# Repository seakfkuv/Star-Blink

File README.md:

# Star-Blink
Star shaped print with 30 RGB-LEDs

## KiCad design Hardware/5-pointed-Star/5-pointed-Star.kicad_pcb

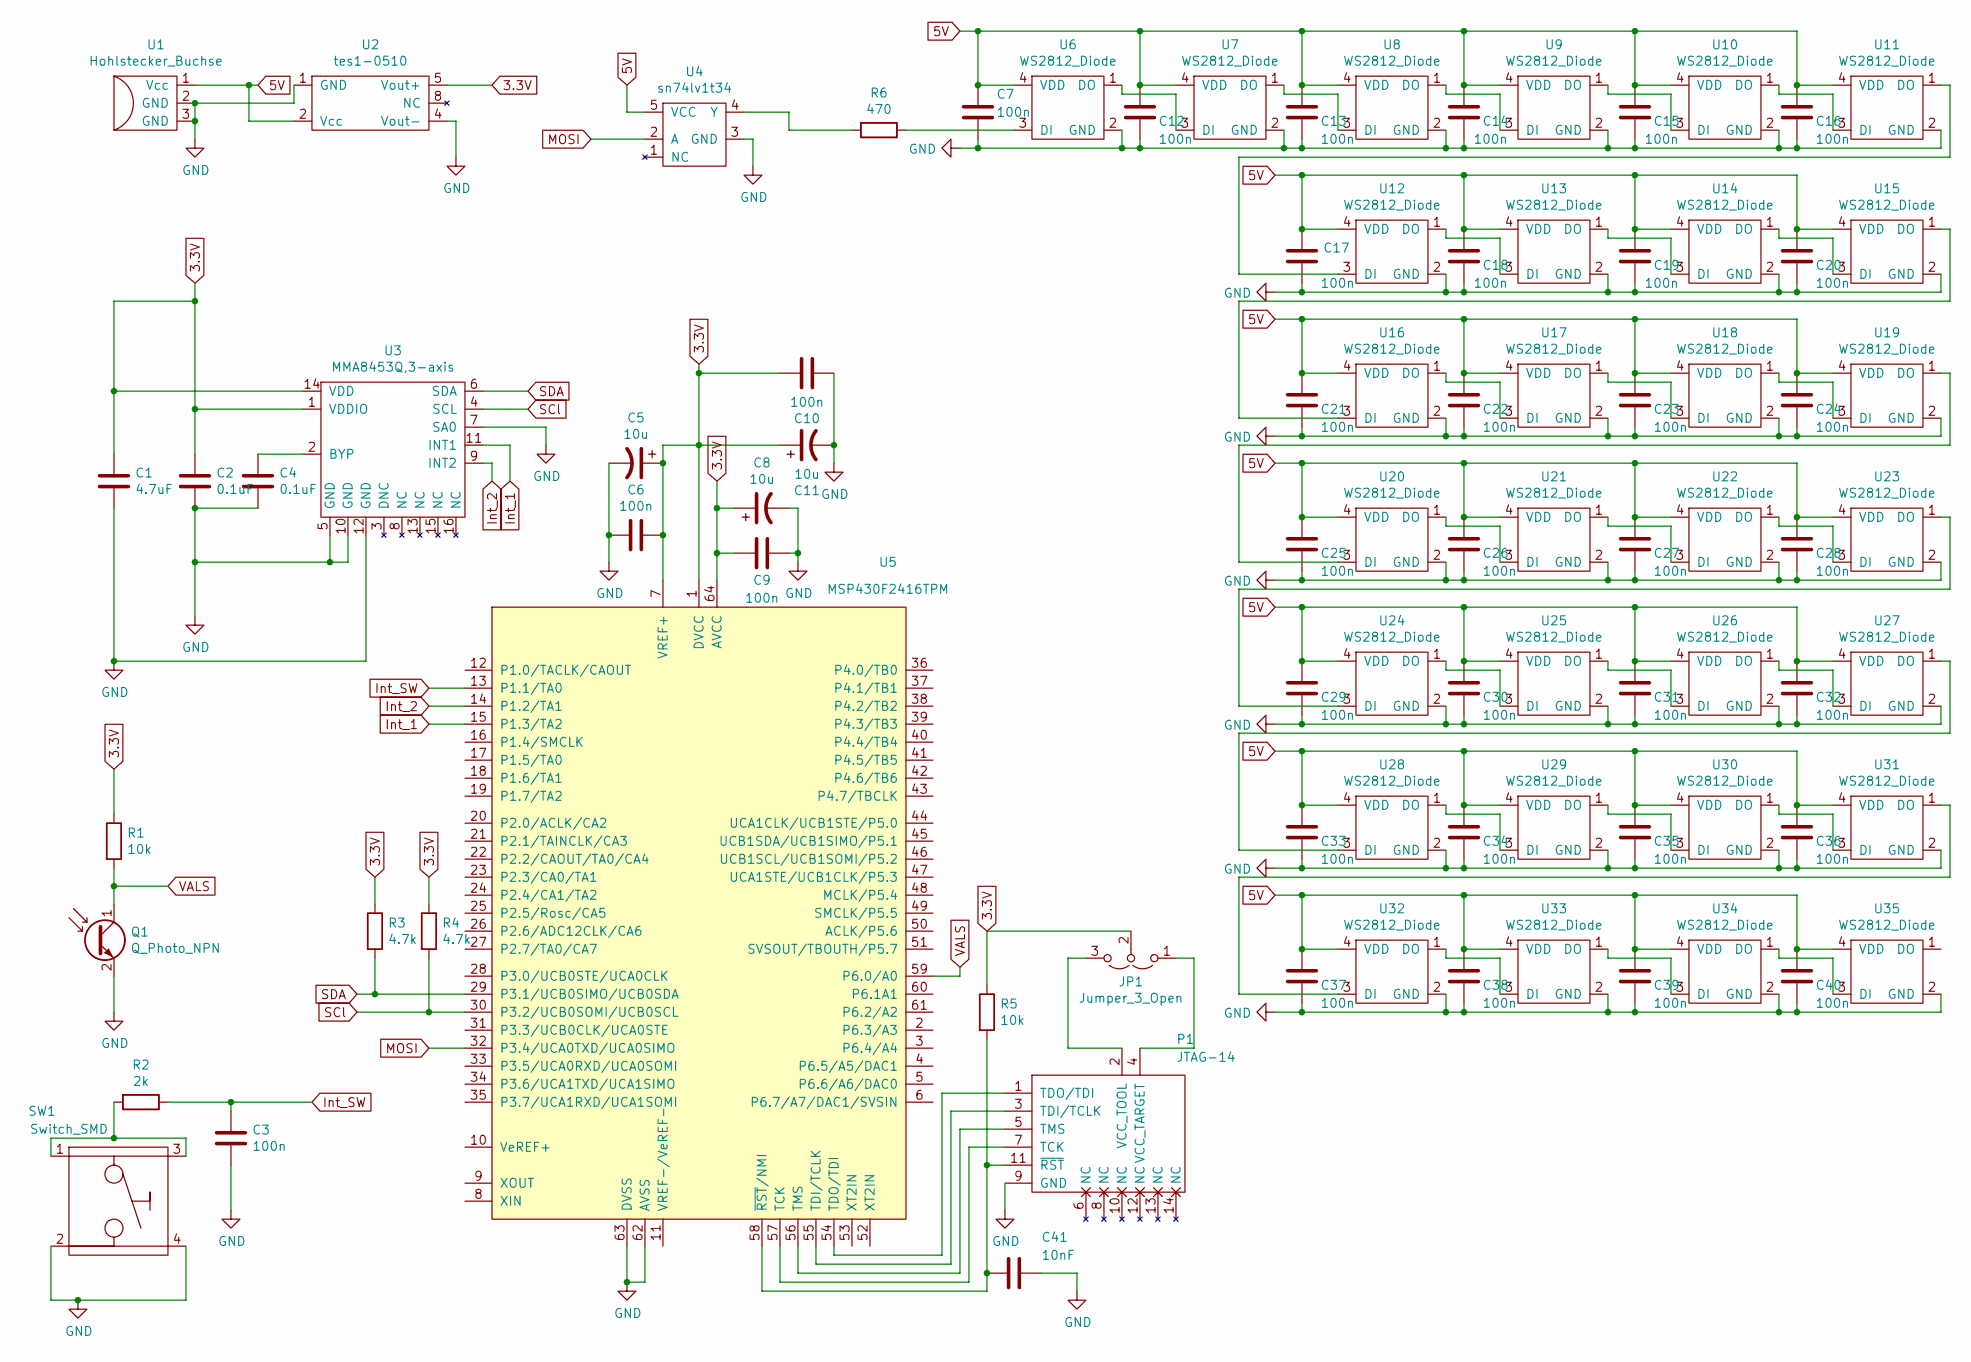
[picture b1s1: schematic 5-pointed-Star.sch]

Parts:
C1: 4.7uF; C_0603_1608Metric
C2, C4: 0.1uF; C_0603_1608Metric
C3, C6, C7, C9, C10, C12, C13, C14, C15, C16, C17, C18, C19, C20, C21, C22, C23, C24, C25, C26, C27, C28, C29, C30, C31, C32, C33, C34, C35, C36, C37, C38, C39, C40: 100n; C_0603_1608Metric
C5, C8, C11: 10u; 865090368008
C41: 10nF; C_0603_1608Metric
JP1: Jumper_3_Open; Jumper_2.54
P1: JTAG-14; JTAG_14
Q1: Q_Photo_NPN; D_0805_2012Metric
R1: 10k; R_0603_1608Metric
R2: 2k; R_0603_1608Metric
R3, R4: 4.7k; R_0603_1608Metric
R5: 10k; R_0603_1608Metric_Pad1.05x0.95mm_HandSolder
R6: 470; R_0603_1608Metric
SW1: Switch_SMD
U1: Hohlstecker_Buchse
U2: tes1-0510
U3: MMA8453Q,3-axis; MMA8453Q
U4: sn74lv1t34; SC70-5
U5: MSP430F2416TPM
U6, U7, U8, U9, U10, U11, U12, U13, U14, U15, U16, U17, U18, U19, U20, U21, U22, U23, U24, U25, U26, U27, U28, U29, U30, U31, U32, U33, U34, U35: WS2812_Diode; WS2812-2020

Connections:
3.3V: C1.1, C2.1, C5.1, C6.1, C8.1, C9.2, C10.1, C11.1, JP1.2 (C), R1.1, R3.1, R4.1, R5.1, U2.5 (Vout+), U3.1 (VDDIO), U3.14 (VDD), U5.1 (DVCC), U5.7 (VREF+), U5.64 (AVCC)
5V: C7.1, C12.1, C13.1, C14.1, C15.1, C16.1, C17.1, C18.1, C19.1, C20.1, C21.1, C22.1, C23.1, C24.1, C25.1, C26.1, C27.1, C28.1, C29.1, C30.1, C31.1, C32.1, C33.1, C34.1, C35.1, C36.1, C37.1, C38.1, C39.1, C40.1, U1.1 (Vcc), U2.2 (Vcc), U4.5 (VCC), U6.4 (VDD), U7.4 (VDD), U8.4 (VDD), U9.4 (VDD), U10.4 (VDD), U11.4 (VDD), U12.4 (VDD), U13.4 (VDD), U14.4 (VDD), U15.4 (VDD), U16.4 (VDD), U17.4 (VDD), U18.4 (VDD), U19.4 (VDD), U20.4 (VDD), U21.4 (VDD), U22.4 (VDD), U23.4 (VDD), U24.4 (VDD), U25.4 (VDD), U26.4 (VDD), U27.4 (VDD), U28.4 (VDD), U29.4 (VDD), U30.4 (VDD), U31.4 (VDD), U32.4 (VDD), U33.4 (VDD), U34.4 (VDD), U35.4 (VDD)
GND: C1.2, C2.2, C3.2, C4.2, C5.2, C6.2, C7.2, C8.2, C9.1, C10.2, C11.2, C12.2, C13.2, C14.2, C15.2, C16.2, C17.2, C18.2, C19.2, C20.2, C21.2, C22.2, C23.2, C24.2, C25.2, C26.2, C27.2, C28.2, C29.2, C30.2, C31.2, C32.2, C33.2, C34.2, C35.2, C36.2, C37.2, C38.2, C39.2, C40.2, C41.1, P1.9 (GND), Q1.2 (E), SW1.2, SW1.4, U1.2 (GND), U1.3 (GND), U2.1 (GND), U2.4 (Vout-), U3.5 (GND), U3.7 (SA0), U3.10 (GND), U3.12 (GND), U4.3 (GND), U5.62 (AVSS), U5.63 (DVSS), U6.2 (GND), U7.2 (GND), U8.2 (GND), U9.2 (GND), U10.2 (GND), U11.2 (GND), U12.2 (GND), U13.2 (GND), U14.2 (GND), U15.2 (GND), U16.2 (GND), U17.2 (GND), U18.2 (GND), U19.2 (GND), U20.2 (GND), U21.2 (GND), U22.2 (GND), U23.2 (GND), U24.2 (GND), U25.2 (GND), U26.2 (GND), U27.2 (GND), U28.2 (GND), U29.2 (GND), U30.2 (GND), U31.2 (GND), U32.2 (GND), U33.2 (GND), U34.2 (GND), U35.2 (GND)
Int_1: U3.11 (INT1), U5.15 (P1.3/TA2)
Int_2: U3.9 (INT2), U5.14 (P1.2/TA1)
Int_SW: C3.1, R2.1, U5.13 (P1.1/TA0)
MOSI: U4.2 (A), U5.32 (P3.4/UCA0TXD/UCA0SIMO)
unnamed: C4.1, U3.2 (BYP)
unnamed: C41.2, P1.11 (~RST), R5.2, U5.58 (~RST~/NMI)
unnamed: JP1.1 (A), P1.4 (VCC_TARGET)
unnamed: JP1.3 (B), P1.2 (VCC_TOOL)
unnamed: P1.1 (TDO/TDI), U5.54 (TDO/TDI)
unnamed: P1.3 (TDI/TCLK), U5.55 (TDI/TCLK)
unnamed: P1.5 (TMS), U5.56 (TMS)
unnamed: P1.7 (TCK), U5.57 (TCK)
unnamed: R2.2, SW1.1, SW1.3
unnamed: R6.1, U6.3 (DI)
unnamed: R6.2, U4.4 (Y)
unnamed: U6.1 (DO), U7.3 (DI)
unnamed: U7.1 (DO), U8.3 (DI)
unnamed: U8.1 (DO), U9.3 (DI)
unnamed: U10.1 (DO), U11.3 (DI)
unnamed: U9.1 (DO), U10.3 (DI)
unnamed: U11.1 (DO), U12.3 (DI)
unnamed: U12.1 (DO), U13.3 (DI)
unnamed: U13.1 (DO), U14.3 (DI)
unnamed: U14.1 (DO), U15.3 (DI)
unnamed: U15.1 (DO), U16.3 (DI)
unnamed: U16.1 (DO), U17.3 (DI)
unnamed: U17.1 (DO), U18.3 (DI)
unnamed: U18.1 (DO), U19.3 (DI)
unnamed: U19.1 (DO), U20.3 (DI)
unnamed: U20.1 (DO), U21.3 (DI)
unnamed: U21.1 (DO), U22.3 (DI)
unnamed: U22.1 (DO), U23.3 (DI)
unnamed: U23.1 (DO), U24.3 (DI)
unnamed: U24.1 (DO), U25.3 (DI)
unnamed: U25.1 (DO), U26.3 (DI)
unnamed: U26.1 (DO), U27.3 (DI)
unnamed: U27.1 (DO), U28.3 (DI)
unnamed: U28.1 (DO), U29.3 (DI)
unnamed: U29.1 (DO), U30.3 (DI)
unnamed: U30.1 (DO), U31.3 (DI)
unnamed: U31.1 (DO), U32.3 (DI)
unnamed: U32.1 (DO), U33.3 (DI)
unnamed: U33.1 (DO), U34.3 (DI)
unnamed: U34.1 (DO), U35.3 (DI)
SCl: R4.2, U3.4 (SCL), U5.30 (P3.2/UCB0SOMI/UCB0SCL)
SDA: R3.2, U3.6 (SDA), U5.29 (P3.1/UCB0SIMO/UCB0SDA)
VALS: Q1.1 (C), R1.2, U5.59 (P6.0/A0)

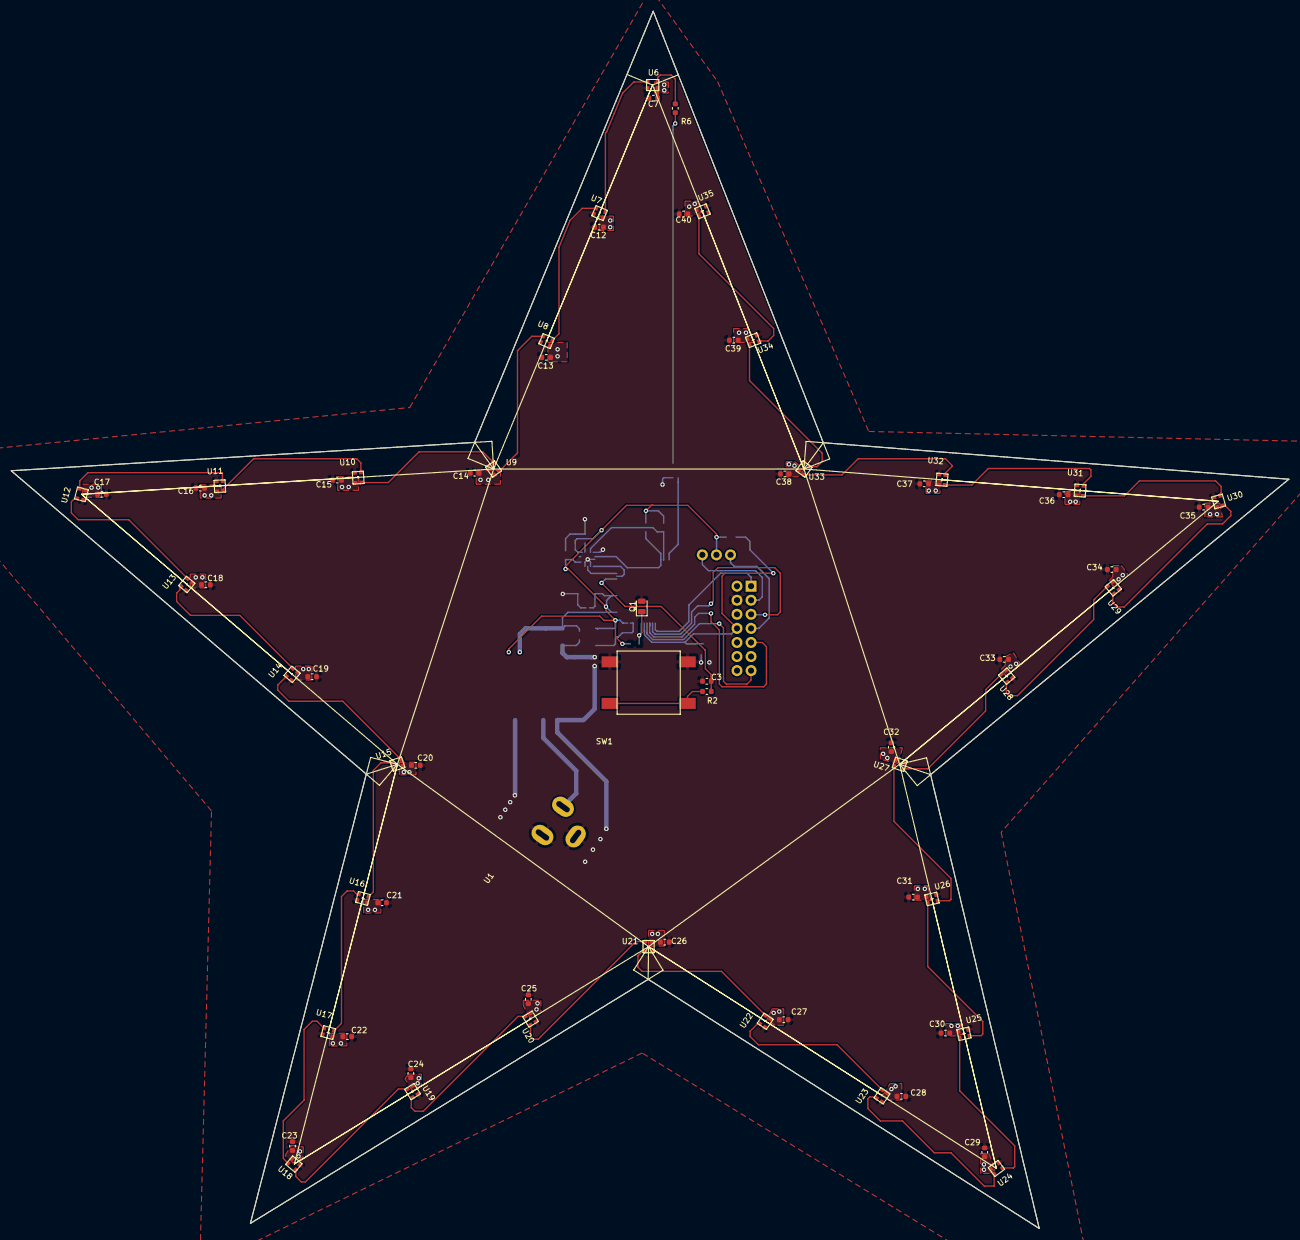
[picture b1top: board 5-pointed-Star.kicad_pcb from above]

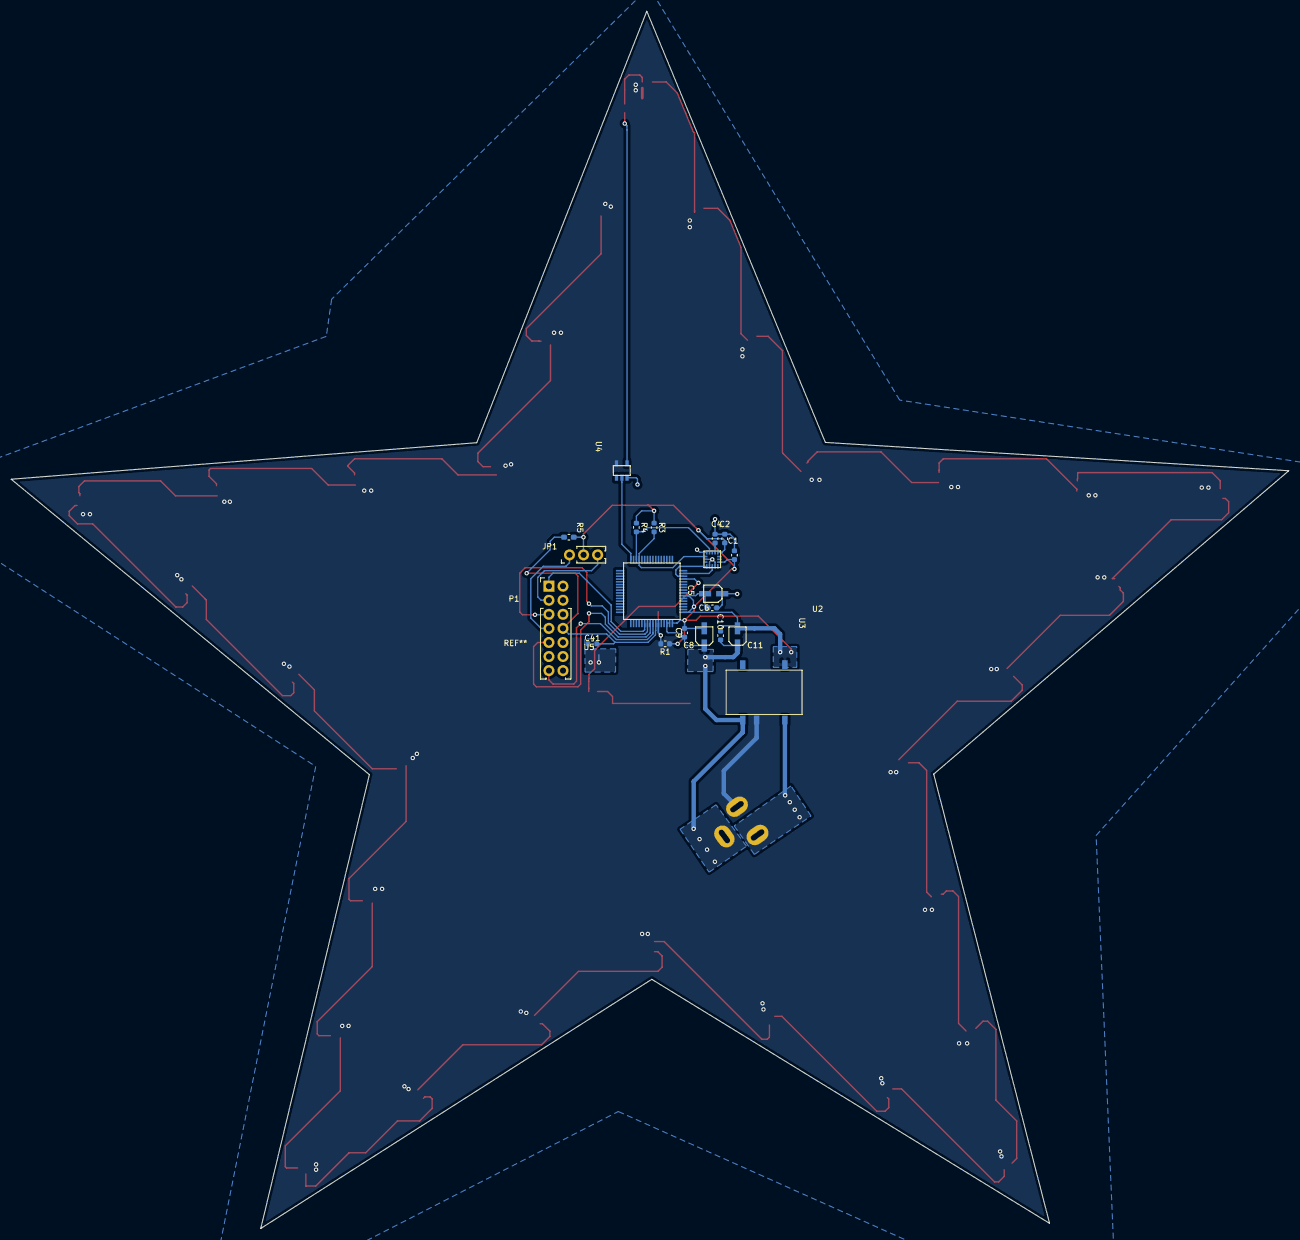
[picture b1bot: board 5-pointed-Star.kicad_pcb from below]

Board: 2 copper layers, 230.6 x 219.7 mm, 86 parts (20 on the bottom side), 50 nets.
